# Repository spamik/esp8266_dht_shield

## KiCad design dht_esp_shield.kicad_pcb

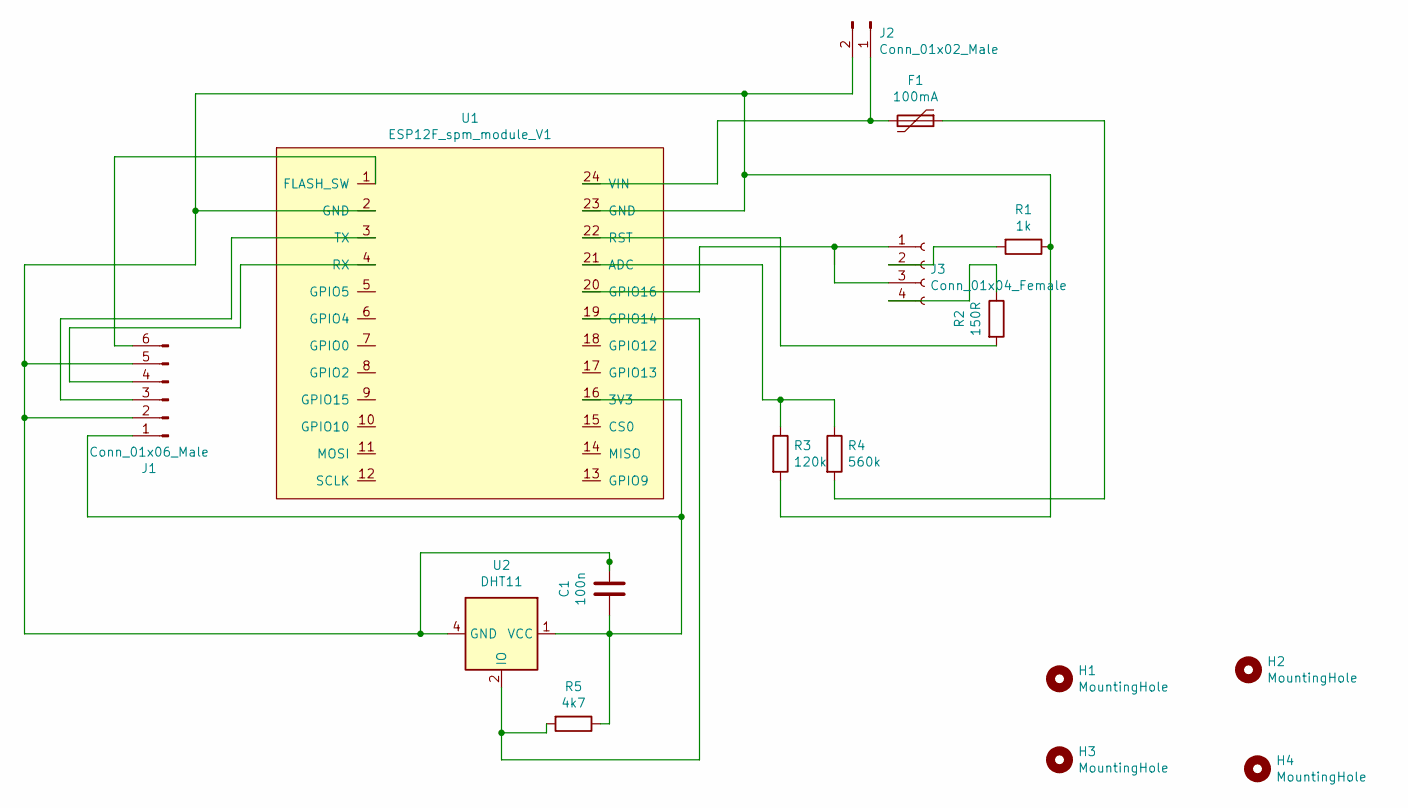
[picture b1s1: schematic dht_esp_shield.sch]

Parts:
C1: 100n; C_0603_1608Metric_Pad1.08x0.95mm_HandSolder
F1: 100mA; Fuse_1812_4532Metric_Pad1.30x3.40mm_HandSolder
H1, H2, H3, H4: MountingHole; MountingHole_2.7mm_M2.5
J1: Conn_01x06_Male; PinHeader_1x06_P2.54mm_Vertical
J2: Conn_01x02_Male; PinHeader_1x02_P2.54mm_Vertical
J3: Conn_01x04_Female; PinHeader_1x04_P2.54mm_Vertical
R1: 1k; R_0805_2012Metric_Pad1.20x1.40mm_HandSolder
R2: 150R; R_0805_2012Metric_Pad1.20x1.40mm_HandSolder
R3: 120k; R_0805_2012Metric_Pad1.20x1.40mm_HandSolder
R4: 560k; R_0805_2012Metric_Pad1.20x1.40mm_HandSolder
R5: 4k7; R_0805_2012Metric_Pad1.20x1.40mm_HandSolder
U1: ESP12F_spm_module_V1; ESP12F_spm_module_v1
U2: DHT11; Aosong_DHT11_5.5x12.0_P2.54mm

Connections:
unnamed: C1.1, J1.2, J1.5, J2.2, R1.1, R3.2, U1.2 (GND), U1.23 (GND), U2.4 (GND)
unnamed: C1.2, J1.1, R5.1, U1.16 (3V3), U2.1 (VCC)
unnamed: F1.1, R4.2
unnamed: F1.2, J2.1, U1.24 (VIN)
unnamed: J1.3, U1.3 (TX)
unnamed: J1.4, U1.4 (RX)
unnamed: J1.6, U1.1 (FLASH_SW)
unnamed: J3.1, J3.3, U1.20 (GPIO16)
unnamed: J3.2, R1.2
unnamed: J3.4, R2.1
unnamed: R2.2, U1.22 (RST)
unnamed: R3.1, R4.1, U1.21 (ADC)
unnamed: R5.2, U1.19 (GPIO14), U2.2 (IO)

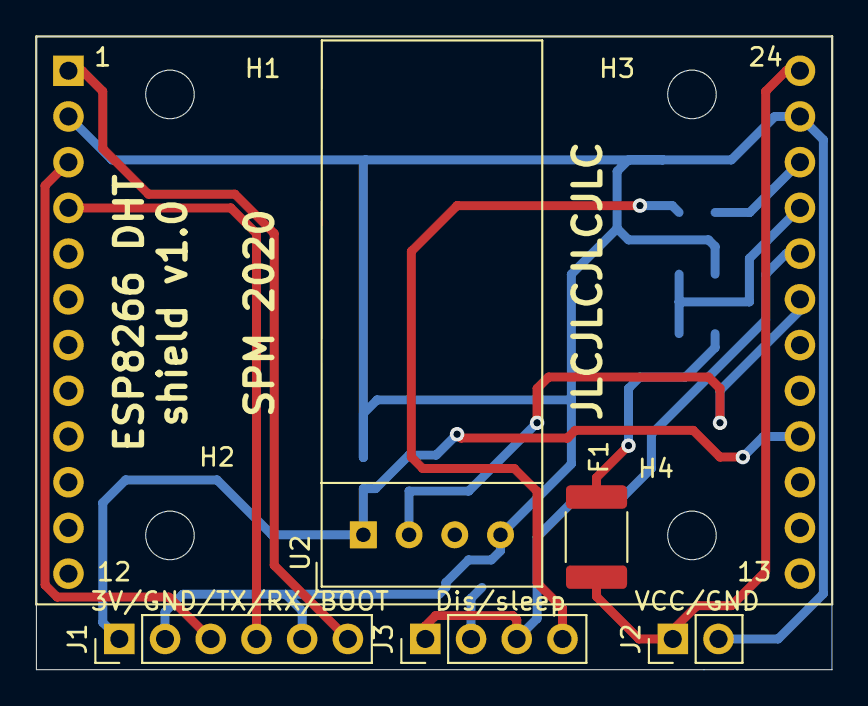
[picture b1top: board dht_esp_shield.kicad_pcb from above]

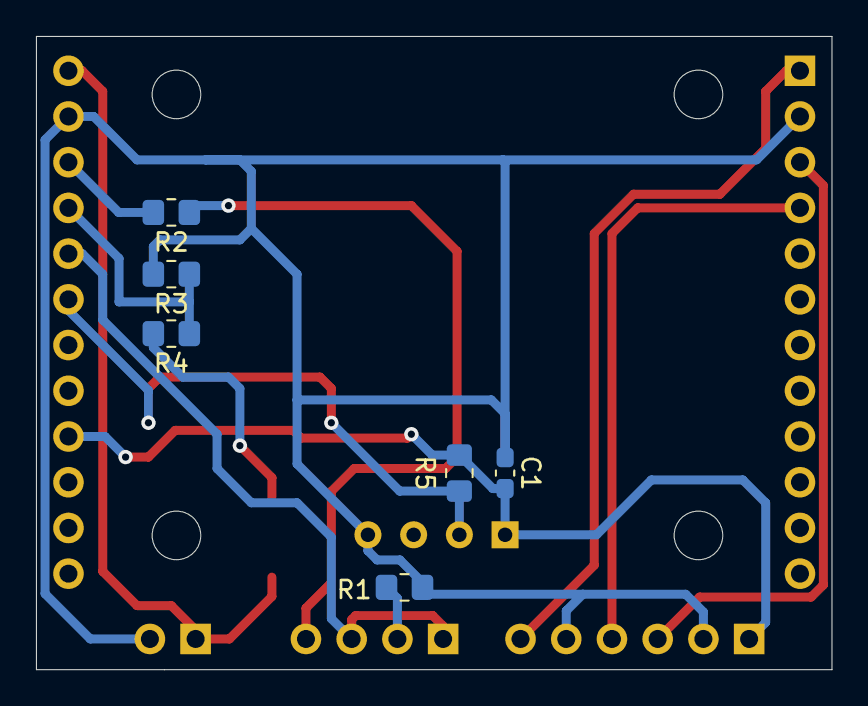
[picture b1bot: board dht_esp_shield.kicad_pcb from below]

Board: 2 copper layers, 44.2 x 35.2 mm, 16 parts (6 on the bottom side), 13 nets.

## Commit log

2021-01-16 initial import
